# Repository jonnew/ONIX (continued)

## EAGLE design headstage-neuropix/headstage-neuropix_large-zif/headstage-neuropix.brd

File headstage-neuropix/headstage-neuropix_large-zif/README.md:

# headstage-neuropix (large ZIF)
This version of the headstage has a larger, more reliable ZIF connector.

## Bill of materials
TODO

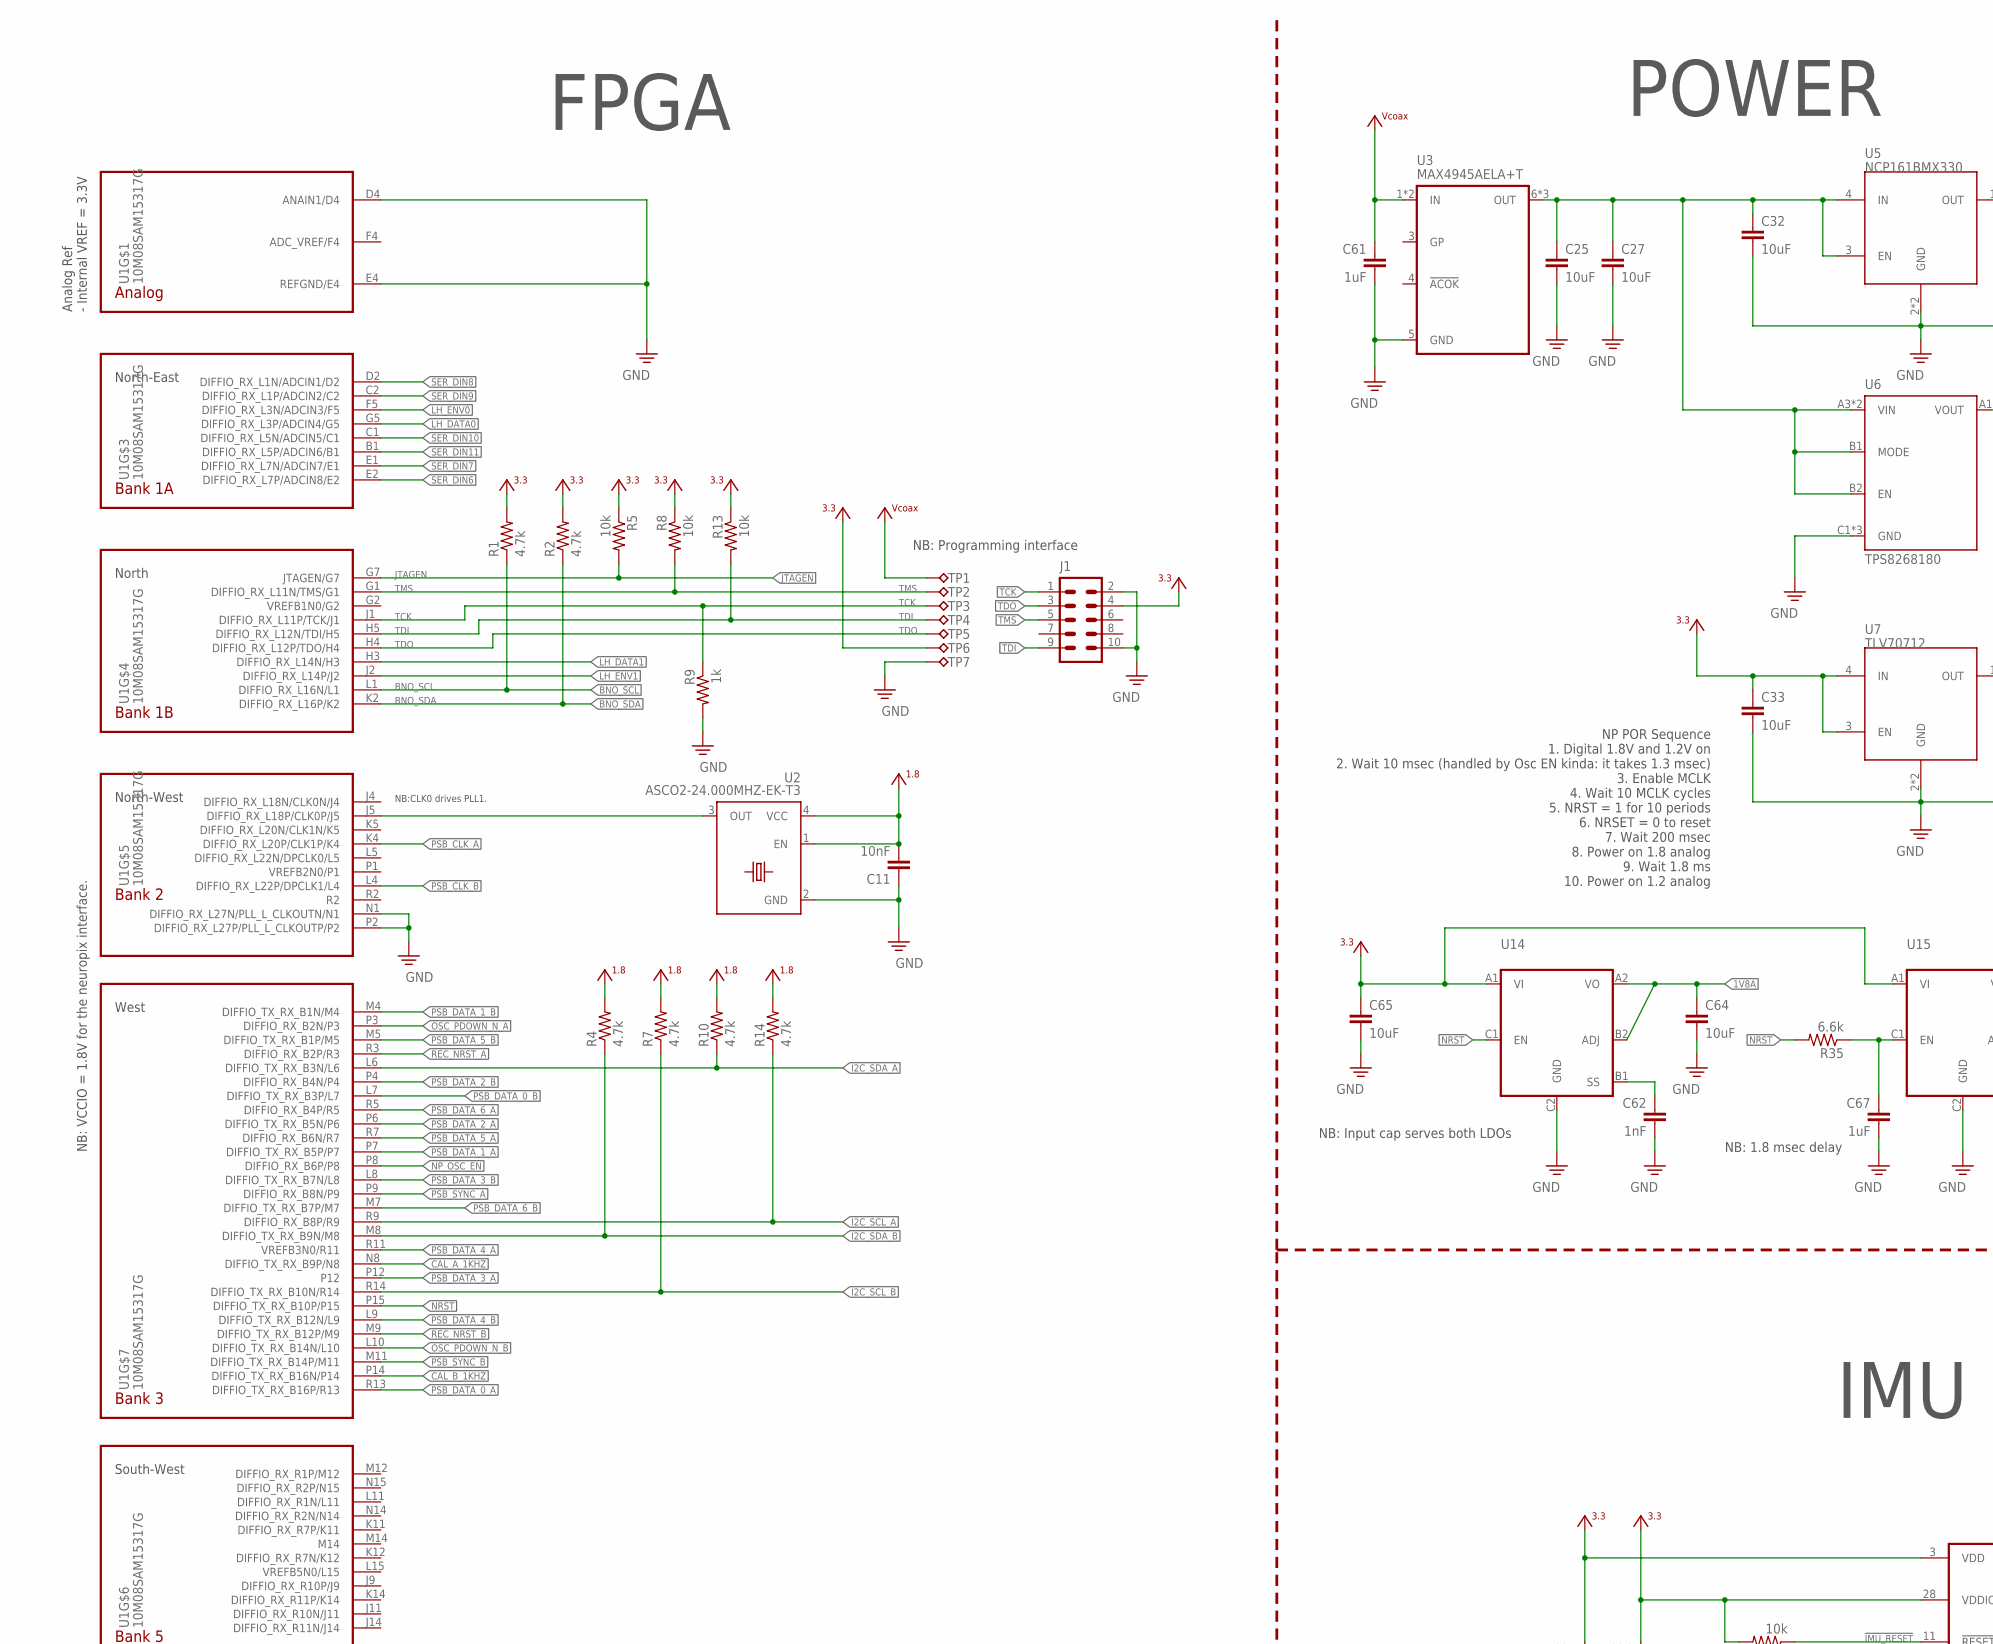
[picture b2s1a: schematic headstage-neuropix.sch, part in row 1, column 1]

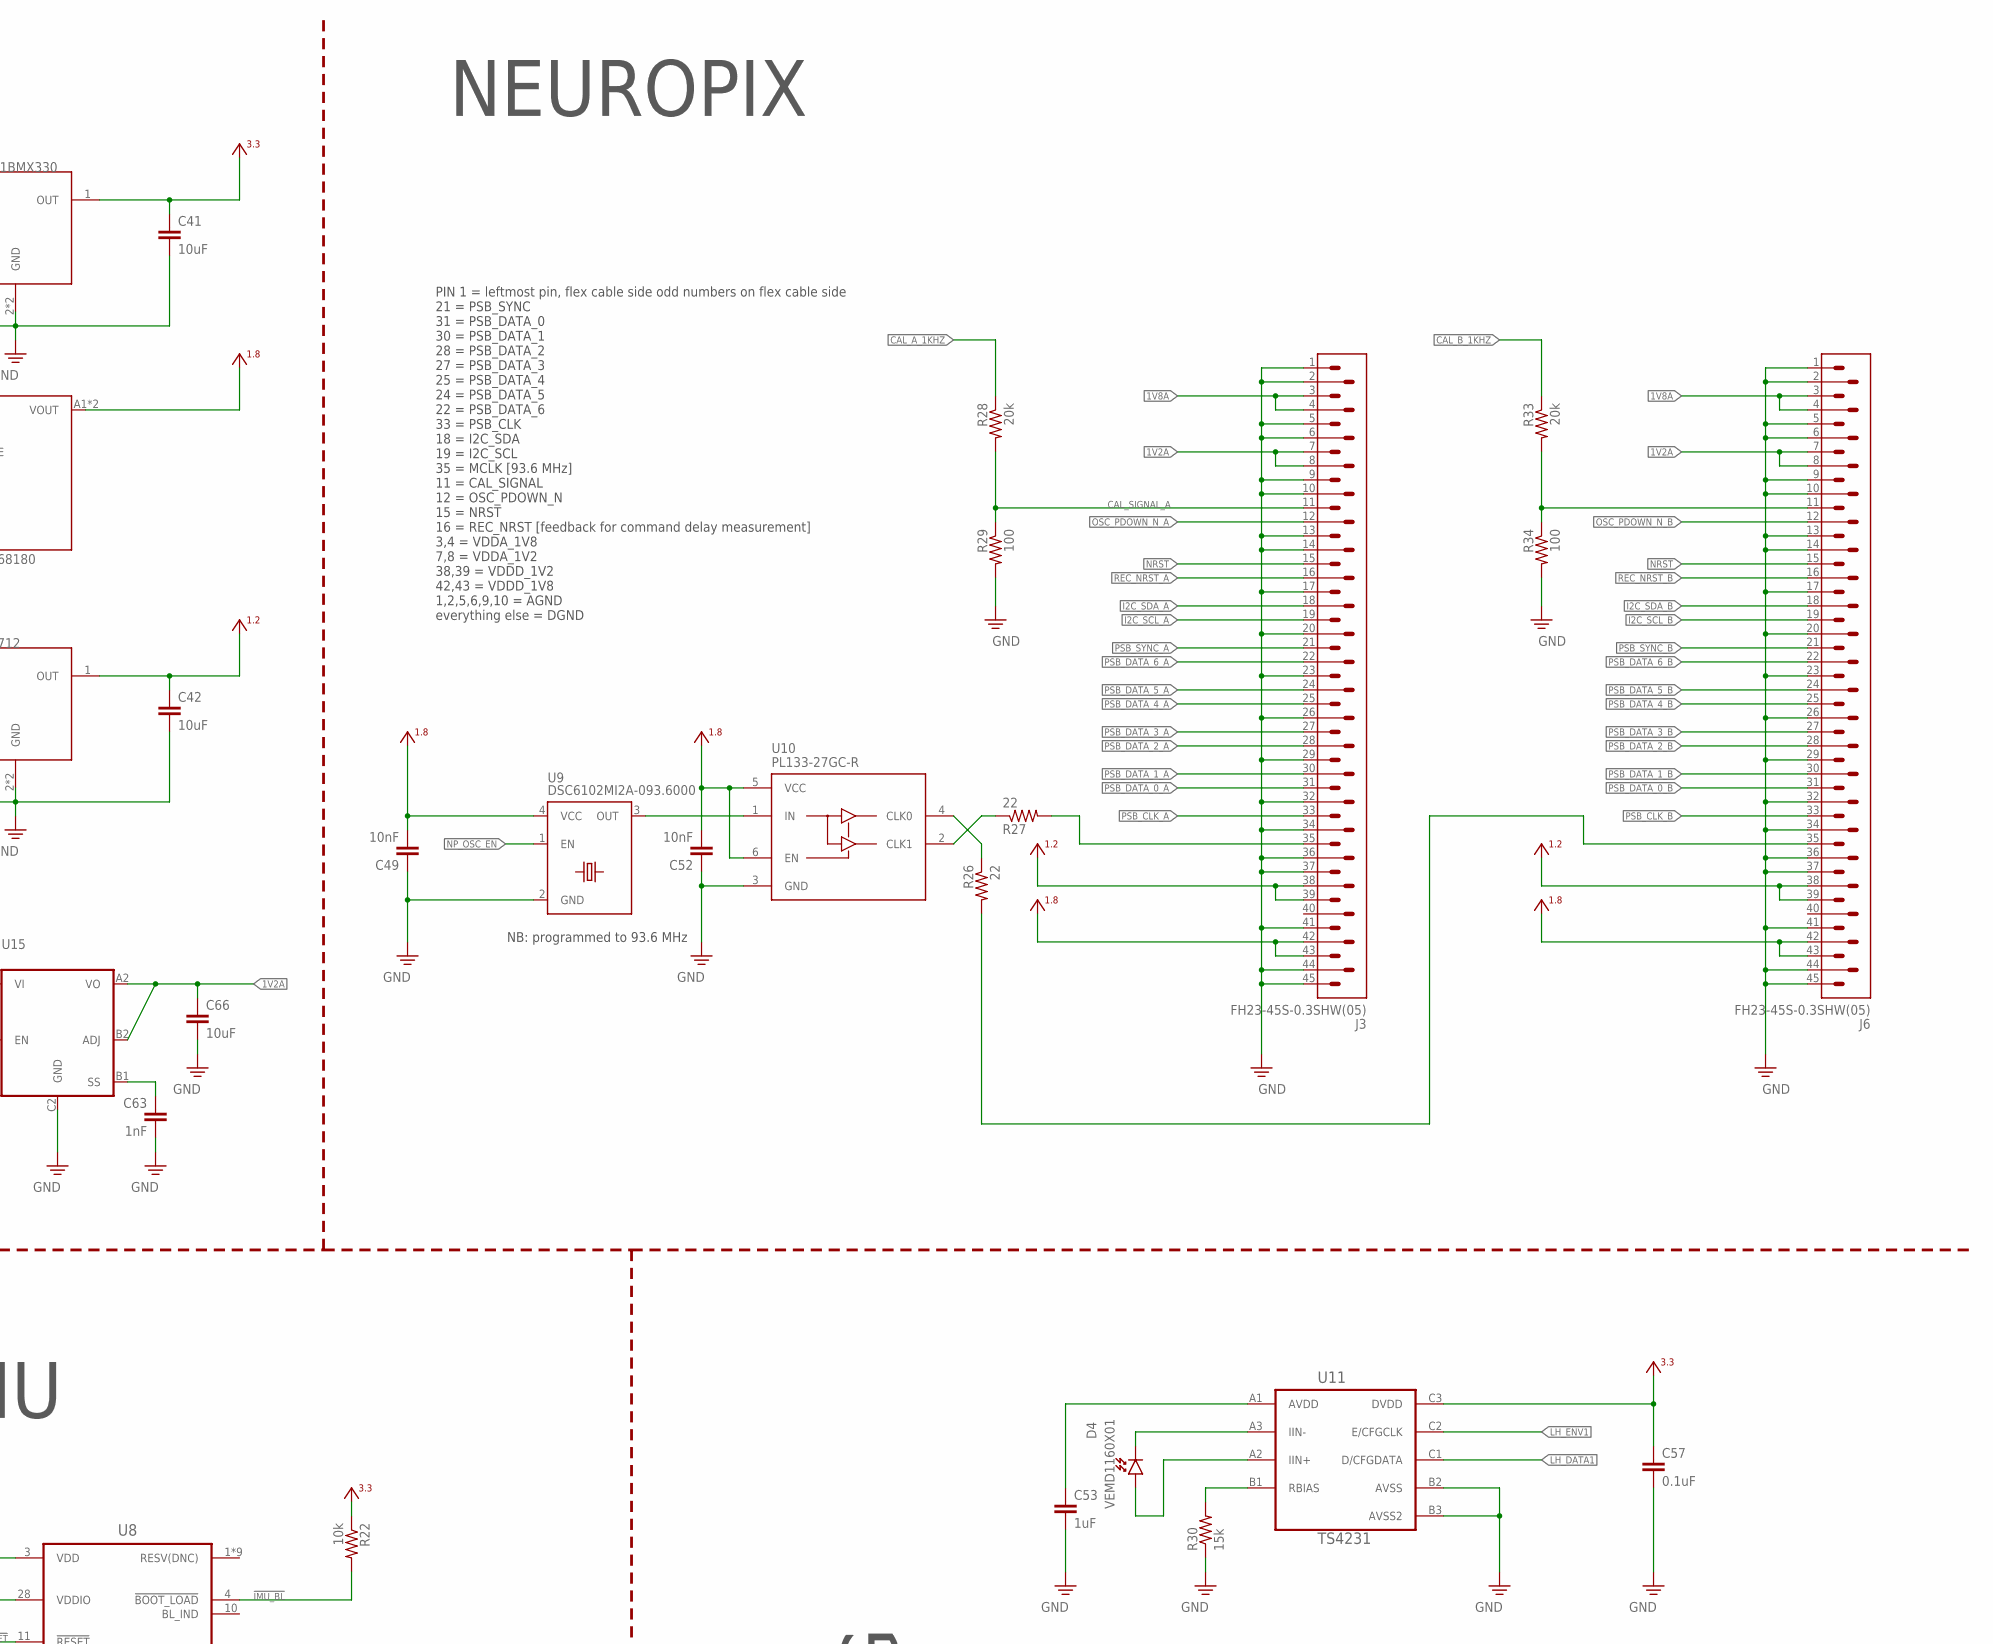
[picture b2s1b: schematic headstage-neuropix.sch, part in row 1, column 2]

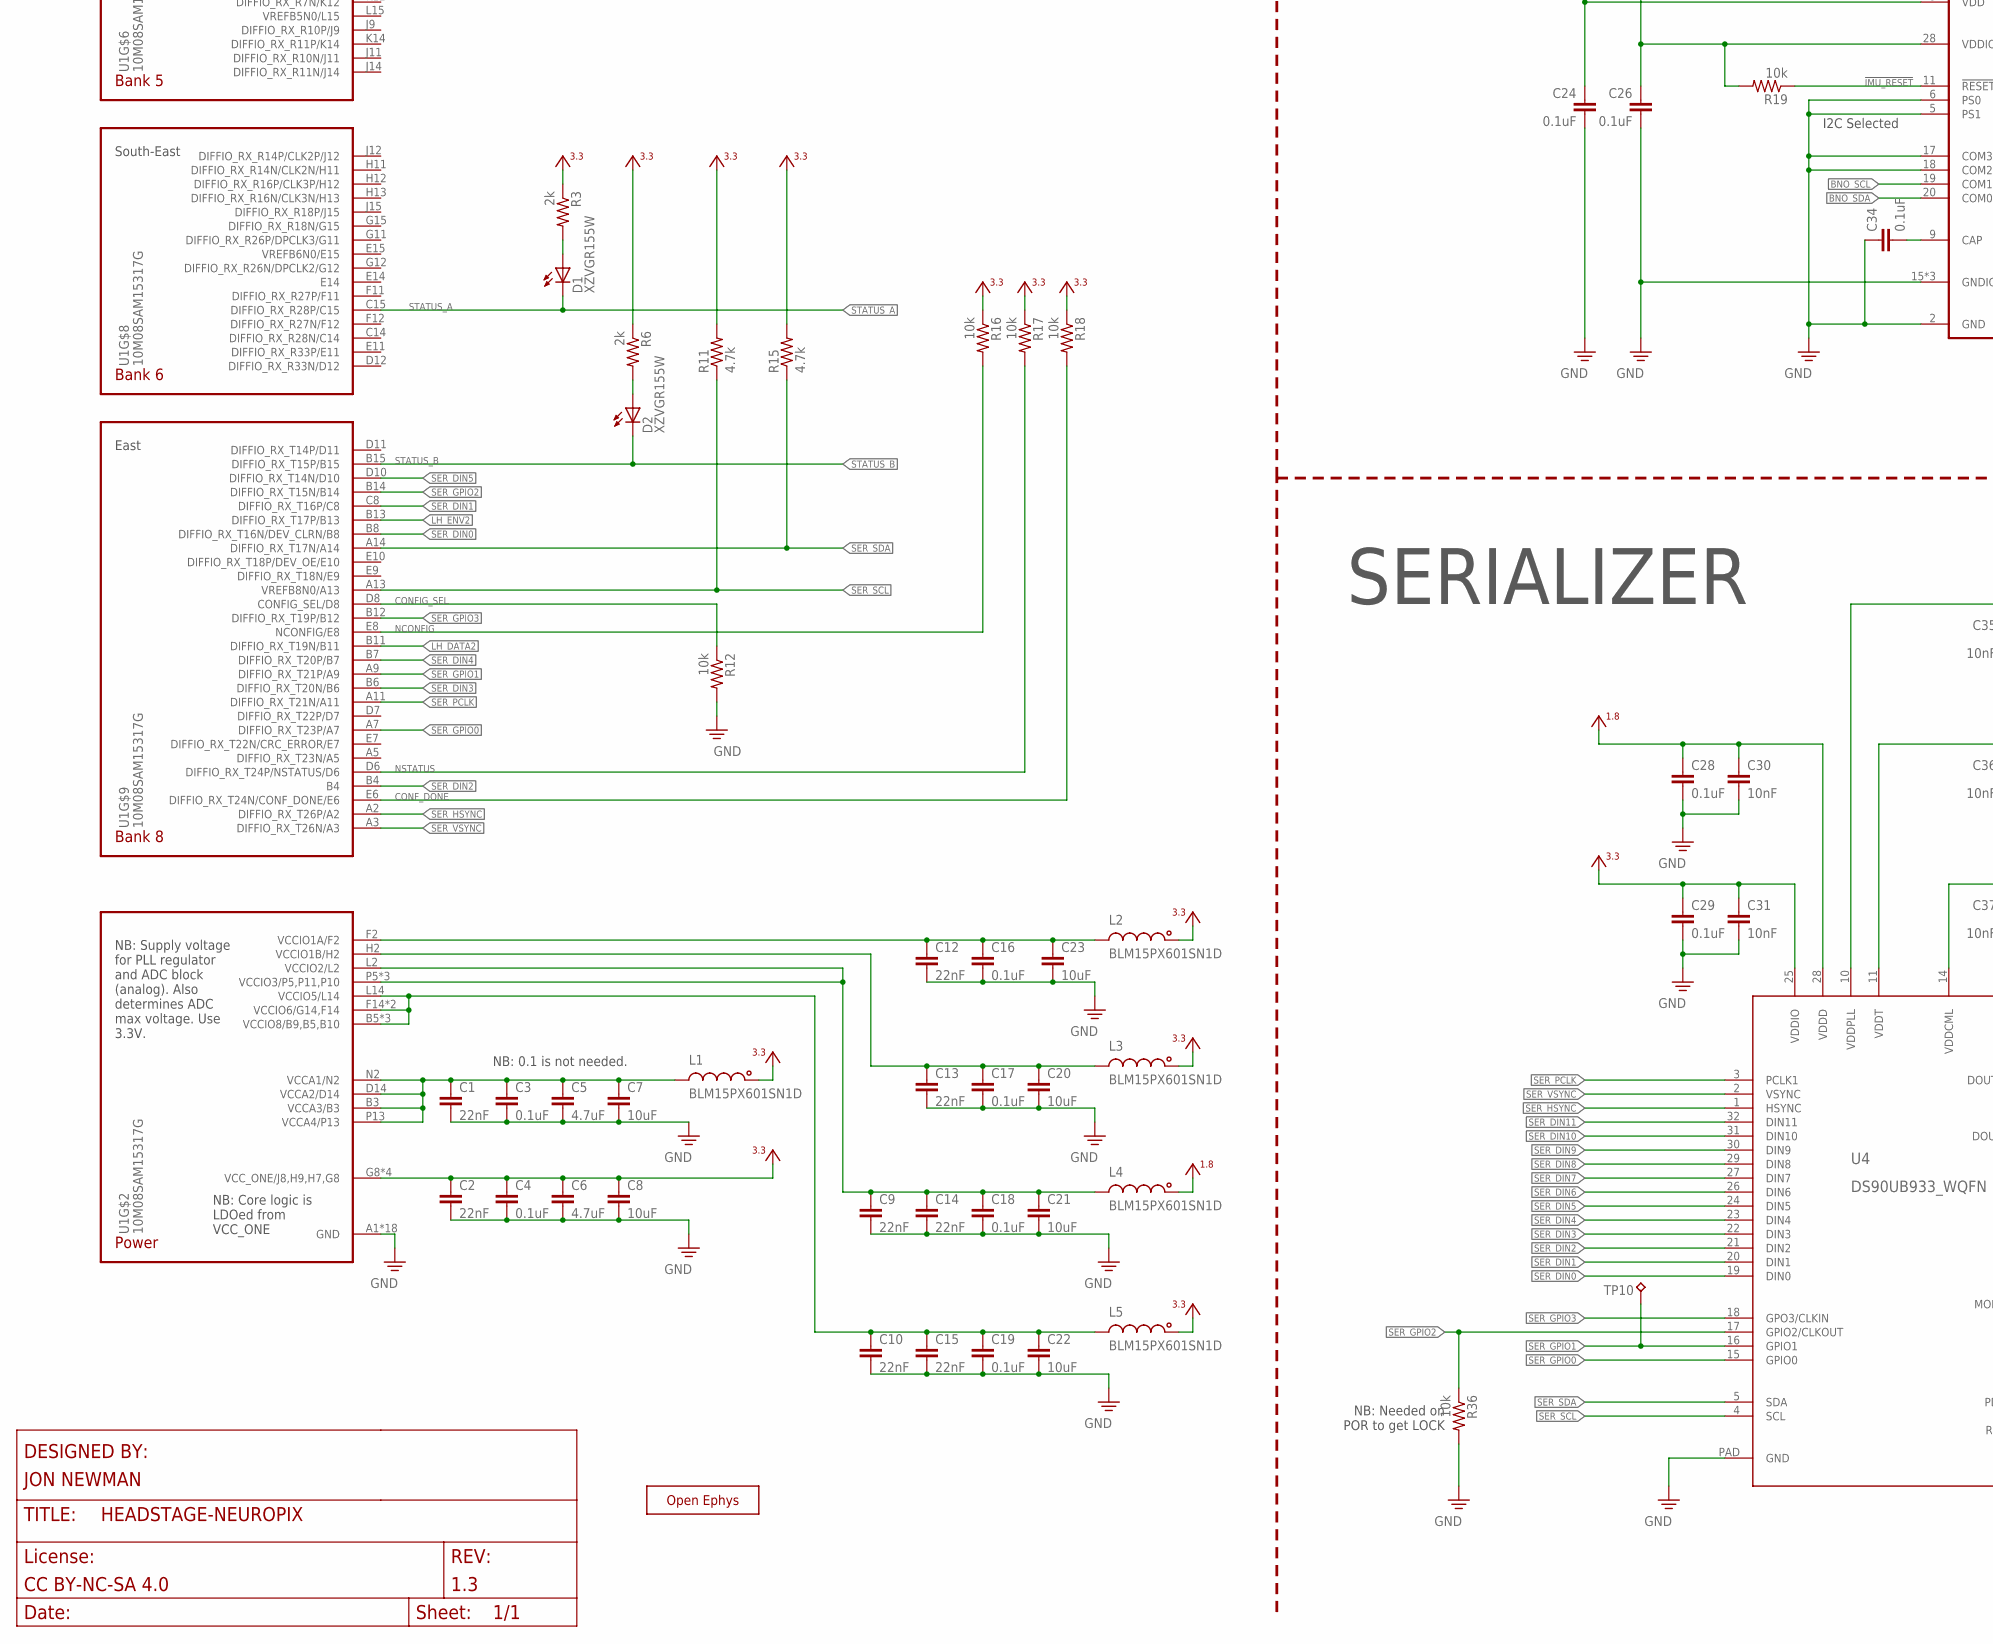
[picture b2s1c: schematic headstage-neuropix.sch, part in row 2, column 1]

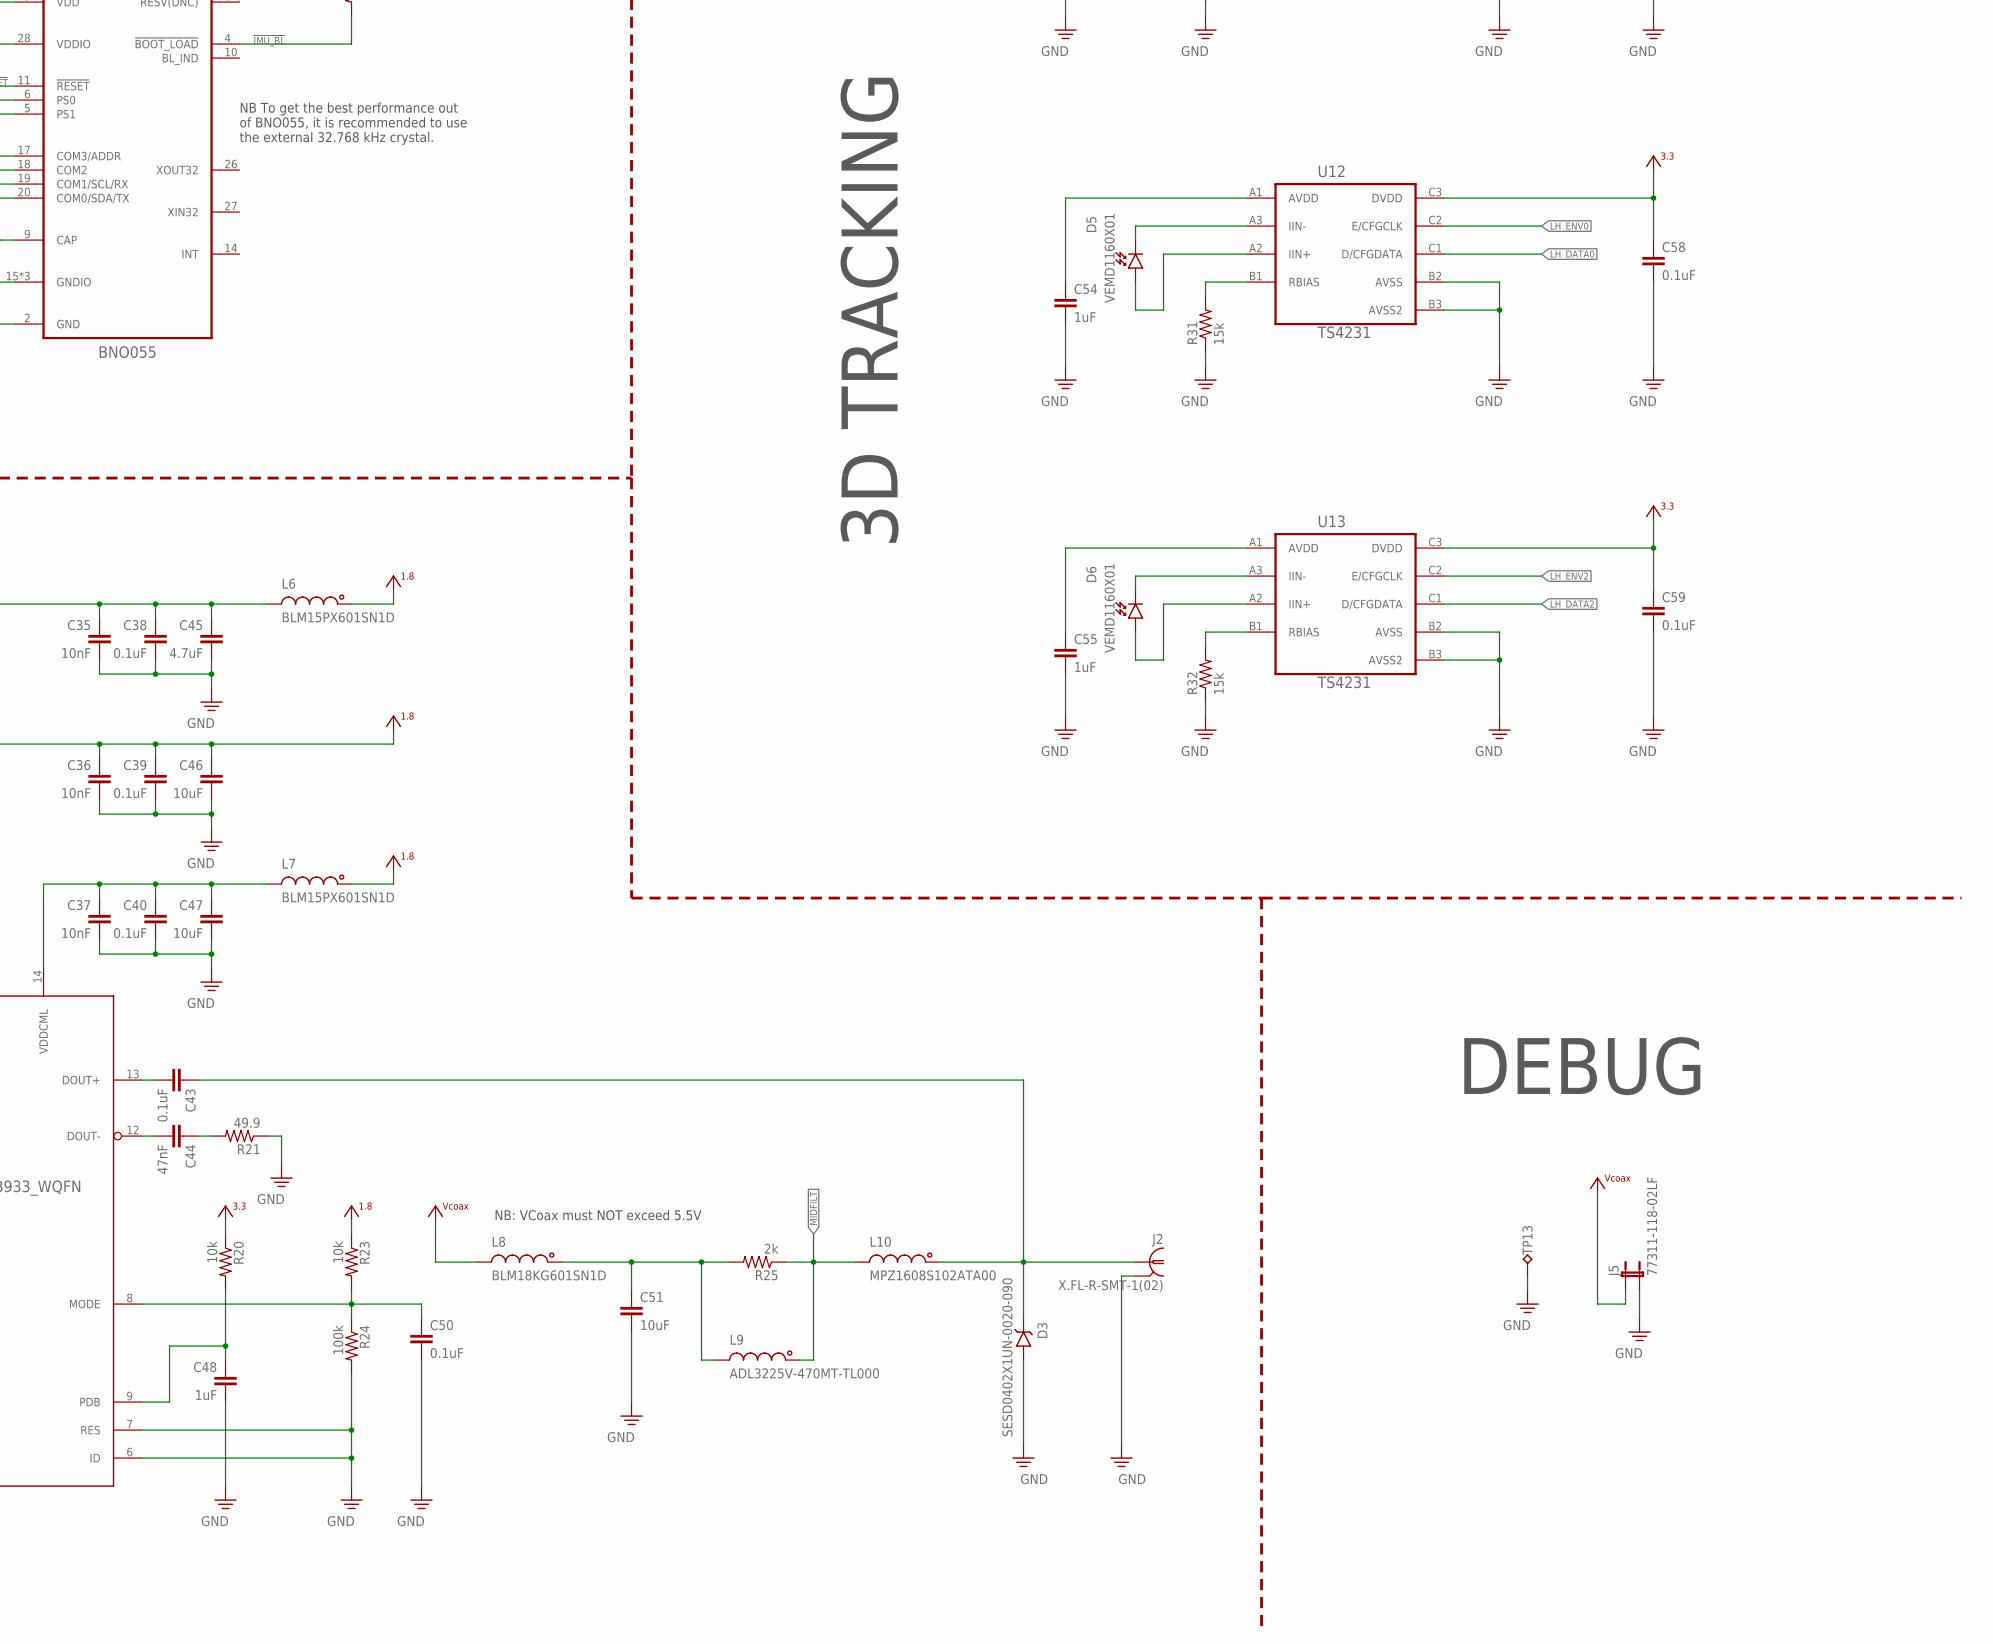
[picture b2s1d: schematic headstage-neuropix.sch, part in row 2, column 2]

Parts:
C1, C2, C9, C10, C12, C13, C14, C15: 22nF; 0201T
C3, C4, C16, C17, C18, C19, C24, C26, C28, C29, C34, C38, C39, C40, C43, C50: 0.1uF; 0201T
C5, C6, C45: 4.7uF; 0402T
C7, C8, C20, C21, C22, C23, C46, C51: 10uF; 0402T
C11, C30, C31, C35, C36, C37, C49, C52: 10nF; 0201T
C25, C27, C32, C33, C41, C42, C47, C64, C65, C66: 10uF; 0402TW
C44: 47nF; 0201T
C48, C61, C67: 1uF; 0201T
C53, C54, C55: 1uF; 0201T; PARTNO CL03A105MP3ZSNH
C57, C58, C59: 0.1uF; 0201T; PARTNO C0603X5R1C104K030BC
C62, C63: 1nF; 0201T
D1, D2: XZVGR155W; LED-0201T
D3: SESD0402X1UN-0020-090; 0402T-DFN
D4, D5, D6: VEMD1160X01; 0805PT-NOSILK
J1: 302-S101; 2X05_IDC
J2: X.FL-R-SMT-1(02); X_FL_R_SMT_1(02)
J3, J6: FH23-45S-0.3SHW(05)
J5: 77311-118-02LF; JP2
L1, L2, L3, L4, L5, L6, L7: BLM15PX601SN1D; 0402T
L8: BLM18KG601SN1D; 0603T
L9: ADL3225V-470MT-TL000; 1210T
L10: MPZ1608S102ATA00; 0603T
R1, R2, R4, R7, R10, R11, R14, R15: 4.7k; 0201T
R3, R6, R25: 2k; 0201T
R5, R8, R12, R13, R16, R17, R18, R19, R20, R22, R23, R36: 10k; 0201T
R9: 1k; 0201T
R21: 49.9; 0201T
R24: 100k; 0201T
R26, R27: 22; 0201T
R28, R33: 20k; 0201T
R29, R34: 100; 0201T
R30, R31, R32: 15k; 0201T
R35: 6.6k; 0201T
TP1, TP2, TP3, TP4, TP5, TP6, TP7: TPTP10R; TP10R
TP10: TPTP09R; TP09R
TP13: TPTP20R; TP20R
U1: 10M08SAM15317G; MBGA153-8X8
U2: ASCO2-24.000MHZ-EK-T3; ASCO
U3: MAX4945AELA+T; UDFN8-2X2
U4: DS90UB933_WQFN; WQFN32-5X5
U5: NCP161BMX330; X2SON
U6: TPS8268180; MICROSIP9-3X2.3
U7: TLV70712; X2SON
U8: BNO055; LGA-28-3.8X5.2
U9: DSC6102MI2A-093.6000; VFLGA4-2.0X1.6
U10: PL133-27GC-R; DFN6_2X1.3_PAD
U11, U12, U13: TS4231; WLCSP3X3
U14, U15: LDO_ADJUST-EN-SS_WLCSP-ADP7112; WLCSP6-1X1.2
X2: OE-LOGO_14X10; OE-LOGO-14X10

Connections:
1V2A: C66.1, J3.7, J3.8, J6.7, J6.8, U15.A2 (VO), U15.B2 (ADJ)
1V8A: C64.1, J3.3, J3.4, J6.3, J6.4, U14.A2 (VO), U14.B2 (ADJ)
24MHZ_P: U1.J5 (DIFFIO_RX_L18P/CLK0P/J5), U2.3 (OUT)
!IMU_BL: R22.2, U8.4 (!BOOT_LOAD)
!IMU_RESET: R19.1, U8.11 (!RESET)
+1V2: C42.1, J3.38, J3.39, J6.38, J6.39, U7.1 (OUT)
+1V8: C11.2, C28.1, C30.1, C36.1, C39.1, C46.1, C49.2, C52.2, J3.42, J3.43, J6.42, J6.43, L4.1, L6.1, L7.1, R4.2, R7.2, R10.2, R14.2, R23.1, U2.1 (EN), U2.4 (VCC), U4.11 (VDDT), U4.28 (VDDD), U6.A1 (VOUT), U6.A2 (VOUT), U9.4 (VCC), U10.5 (VCC), U10.6 (EN)
+3V3: C2.1, C4.1, C6.1, C8.1, C24.1, C26.1, C29.1, C31.1, C33.1, C41.1, C57.1, C58.1, C59.1, C65.1, J1.4, L1.1, L2.1, L3.1, L5.1, R1.2, R2.2, R3.1, R5.1, R6.1, R8.1, R11.2, R13.1, R15.2, R16.1, R17.1, R18.1, R19.2, R20.1, R22.1, TP6.TP, U1.G8 (VCC_ONE/J8,H9,H7,G8), U1.H7 (VCC_ONE/J8,H9,H7,G8), U1.H9 (VCC_ONE/J8,H9,H7,G8), U1.J8 (VCC_ONE/J8,H9,H7,G8), U4.25 (VDDIO), U5.1 (OUT), U7.3 (EN), U7.4 (IN), U8.3 (VDD), U8.28 (VDDIO), U11.C3 (DVDD), U12.C3 (DVDD), U13.C3 (DVDD), U14.A1 (VI), U15.A1 (VI)
BNO_SCL: R1.1, U1.L1 (DIFFIO_RX_L16N/L1), U8.19 (COM1/SCL/RX)
BNO_SDA: R2.1, U1.K2 (DIFFIO_RX_L16P/K2), U8.20 (COM0/SDA/TX)
CAL_A_1KHZ: R28.1, U1.N8 (DIFFIO_TX_RX_B9P/N8)
CAL_B_1KHZ: R33.1, U1.P14 (DIFFIO_TX_RX_B16N/P14)
CAL_SIGNAL_A: J3.11, R28.2, R29.1
CAL_SIGNAL_A1: J6.11, R33.2, R34.1
CONFIG_SEL: R12.1, U1.D8 (CONFIG_SEL/D8)
CONF_DONE: R18.2, U1.E6 (DIFFIO_RX_T24N/CONF_DONE/E6)
GND: C1.2, C2.2, C3.2, C4.2, C5.2, C6.2, C7.2, C8.2, C9.2, C10.2, C11.1, C12.2, C13.2, C14.2, C15.2, C16.2, C17.2, C18.2, C19.2, C20.2, C21.2, C22.2, C23.2, C24.2, C25.2, C26.2, C27.2, C28.2, C29.2, C30.2, C31.2, C32.2, C33.2, C34.1, C35.2, C36.2, C37.2, C38.2, C39.2, C40.2, C41.2, C42.2, C45.2, C46.2, C47.2, C48.2, C49.1, C50.2, C51.2, C52.1, C53.2, C54.2, C55.2, C57.2, C58.2, C59.2, C61.2, C62.2, C63.2, C64.2, C65.2, C66.2, C67.2, D3.A, J1.2, J1.10, J2.P$2 (2), J2.P$3 (2), J2.P$4 (2), J3.1, J3.2, J3.5, J3.6, J3.9, J3.10, J3.13, J3.14, J3.17, J3.20, J3.23, J3.26, J3.29, J3.32, J3.34, J3.36, J3.37, J3.41, J3.44, J3.45, J5.2, J6.1, J6.2, J6.5, J6.6, J6.9, J6.10, J6.13, J6.14, J6.17, J6.20, J6.23, J6.26, J6.29, J6.32, J6.34, J6.36, J6.37, J6.41, J6.44, J6.45, R9.2, R12.2, R21.1, R24.2, R29.2, R30.1, R31.1, R32.1, R34.2, R36.2, TP7.TP, TP13.TP, U1.A1 (GND), U1.A15 (GND), U1.B2 (GND), U1.D4 (ANAIN1/D4), U1.D5 (GND), U1.D9 (GND), U1.E4 (REFGND/E4), U1.E5 (GND), U1.E12 (GND), U1.G4 (GND), U1.G9 (GND), U1.H8 (GND), U1.H14 (GND), U1.J7 (GND), U1.L12 (GND), U1.M2 (GND), U1.M6 (GND), U1.M10 (GND), U1.N1 (DIFFIO_RX_L27N/PLL_L_CLKOUTN/N1), U1.P2 (DIFFIO_RX_L27P/PLL_L_CLKOUTP/P2), U1.R1 (GND), U1.R15 (GND), U2.2 (GND), U3.5 (GND), U4.6 (ID), U4.7 (RES), U4.PAD (GND), U5.2 (GND), U5.PAD (GND), U6.C1 (GND), U6.C2 (GND), U6.C3 (GND), U7.2 (GND), U7.PAD (GND), U8.2 (GND), U8.5 (PS1), U8.6 (PS0), U8.15 (GNDIO), U8.16 (GNDIO), U8.17 (COM3/ADDR), U8.18 (COM2), U8.25 (GNDIO), U9.2 (GND), U10.3 (GND), U11.B2 (AVSS), U11.B3 (AVSS2), U12.B2 (AVSS), U12.B3 (AVSS2), U13.B2 (AVSS), U13.B3 (AVSS2), U14.C2 (GND), U15.C2 (GND)
I2C_SCL_A: J3.19, R14.1, U1.R9 (DIFFIO_RX_B8P/R9)
I2C_SCL_B: J6.19, R7.1, U1.R14 (DIFFIO_TX_RX_B10N/R14)
I2C_SDA_A: J3.18, R10.1, U1.L6 (DIFFIO_TX_RX_B3N/L6)
I2C_SDA_B: J6.18, R4.1, U1.M8 (DIFFIO_TX_RX_B9N/M8)
JTAGEN: R5.2, U1.G7 (JTAGEN/G7)
LH_DATA0: U1.G5 (DIFFIO_RX_L3P/ADCIN4/G5), U12.C1 (D/CFGDATA)
LH_DATA1: U1.H3 (DIFFIO_RX_L14N/H3), U11.C1 (D/CFGDATA)
LH_DATA2: U1.B11 (DIFFIO_RX_T19N/B11), U13.C1 (D/CFGDATA)
LH_ENV0: U1.F5 (DIFFIO_RX_L3N/ADCIN3/F5), U12.C2 (E/CFGCLK)
LH_ENV1: U1.J2 (DIFFIO_RX_L14P/J2), U11.C2 (E/CFGCLK)
LH_ENV2: U1.B13 (DIFFIO_RX_T17P/B13), U13.C2 (E/CFGCLK)
MIDFILT: L9.1, L10.2, R25.1
unnamed: U9.3 (OUT), U10.1 (IN)
unnamed: R26.1, U10.4 (CLK0)
unnamed: J3.35, R27.2
unnamed: C13.1, C17.1, C20.1, L3.2, U1.H2 (VCCIO1B/H2)
unnamed: J6.35, R26.2
unnamed: R27.1, U10.2 (CLK1)
unnamed: D4.C, U11.A3 (IIN-)
unnamed: D4.A, U11.A2 (IIN+)
unnamed: R30.2, U11.B1 (RBIAS)
unnamed: C53.1, U11.A1 (AVDD)
unnamed: C51.1, L8.1, L9.2, R25.2
unnamed: D5.C, U12.A3 (IIN-)
unnamed: D5.A, U12.A2 (IIN+)
unnamed: R31.2, U12.B1 (RBIAS)
unnamed: D6.C, U13.A3 (IIN-)
unnamed: D6.A, U13.A2 (IIN+)
unnamed: C43.2, U4.13 (DOUT+)
unnamed: R32.2, U13.B1 (RBIAS)
unnamed: C48.1, R20.2, U4.9 (PDB)
unnamed: C44.2, U4.12 (DOUT-)
unnamed: C44.1, R21.2
unnamed: C50.1, R23.2, R24.1, U4.8 (MODE)
unnamed: C35.1, C38.1, C45.1, L6.2, U4.10 (VDDPLL)
unnamed: C37.1, C40.1, C47.1, L7.2, U4.14 (VDDCML)
unnamed: C54.1, U12.A1 (AVDD)
unnamed: C55.1, U13.A1 (AVDD)
unnamed: C25.1, C27.1, C32.1, U3.6 (OUT), U3.7 (OUT), U3.8 (OUT), U5.3 (EN), U5.4 (IN), U6.A3 (VIN), U6.B1 (MODE), U6.B2 (EN), U6.B3 (VIN)
unnamed: C62.1, U14.B1 (SS)
unnamed: C63.1, U15.B1 (SS)
unnamed: C67.1, R35.1, U15.C1 (EN)
unnamed: C34.2, U8.9 (CAP)
unnamed: D2.2 (A), R6.2
unnamed: D1.2 (A), R3.2
NCONFIG: R16.2, U1.E8 (NCONFIG/E8)
NP_OSC_EN: U1.P8 (DIFFIO_RX_B6P/P8), U9.1 (EN)
NRST: J3.15, J6.15, R35.2, U1.P15 (DIFFIO_TX_RX_B10P/P15), U14.C1 (EN)
NSTATUS: R17.2, U1.D6 (DIFFIO_RX_T24P/NSTATUS/D6)
OSC_PDOWN_N_A: J3.12, U1.P3 (DIFFIO_RX_B2N/P3)
OSC_PDOWN_N_B: J6.12, U1.L10 (DIFFIO_TX_RX_B14N/L10)
PSB_CLK_A: J3.33, U1.K4 (DIFFIO_RX_L20P/CLK1P/K4)
PSB_CLK_B: J6.33, U1.L4 (DIFFIO_RX_L22P/DPCLK1/L4)
PSB_DATA_0_A: J3.31, U1.R13 (DIFFIO_TX_RX_B16P/R13)
PSB_DATA_0_B: J6.31, U1.L7 (DIFFIO_TX_RX_B3P/L7)
PSB_DATA_1_A: J3.30, U1.P7 (DIFFIO_TX_RX_B5P/P7)
PSB_DATA_1_B: J6.30, U1.M4 (DIFFIO_TX_RX_B1N/M4)
PSB_DATA_2_A: J3.28, U1.P6 (DIFFIO_TX_RX_B5N/P6)
PSB_DATA_2_B: J6.28, U1.P4 (DIFFIO_RX_B4N/P4)
PSB_DATA_3_A: J3.27, U1.P12
PSB_DATA_3_B: J6.27, U1.L8 (DIFFIO_TX_RX_B7N/L8)
PSB_DATA_4_A: J3.25, U1.R11 (VREFB3N0/R11)
PSB_DATA_4_B: J6.25, U1.L9 (DIFFIO_TX_RX_B12N/L9)
PSB_DATA_5_A: J3.24, U1.R7 (DIFFIO_RX_B6N/R7)
PSB_DATA_5_B: J6.24, U1.M5 (DIFFIO_TX_RX_B1P/M5)
PSB_DATA_6_A: J3.22, U1.R5 (DIFFIO_RX_B4P/R5)
PSB_DATA_6_B: J6.22, U1.M7 (DIFFIO_TX_RX_B7P/M7)
PSB_SYNC_A: J3.21, U1.P9 (DIFFIO_RX_B8N/P9)
PSB_SYNC_B: J6.21, U1.M11 (DIFFIO_TX_RX_B14P/M11)
REC_NRST_A: J3.16, U1.R3 (DIFFIO_RX_B2P/R3)
REC_NRST_B: J6.16, U1.M9 (DIFFIO_TX_RX_B12P/M9)
SER_DIN0: U1.B8 (DIFFIO_RX_T16N/DEV_CLRN/B8), U4.19 (DIN0)
SER_DIN1: U1.C8 (DIFFIO_RX_T16P/C8), U4.20 (DIN1)
SER_DIN2: U1.B4, U4.21 (DIN2)
SER_DIN3: U1.B6 (DIFFIO_RX_T20N/B6), U4.22 (DIN3)
SER_DIN4: U1.B7 (DIFFIO_RX_T20P/B7), U4.23 (DIN4)
SER_DIN5: U1.D10 (DIFFIO_RX_T14N/D10), U4.24 (DIN5)
SER_DIN6: U1.E2 (DIFFIO_RX_L7P/ADCIN8/E2), U4.26 (DIN6)
SER_DIN7: U1.E1 (DIFFIO_RX_L7N/ADCIN7/E1), U4.27 (DIN7)
SER_DIN8: U1.D2 (DIFFIO_RX_L1N/ADCIN1/D2), U4.29 (DIN8)
SER_DIN9: U1.C2 (DIFFIO_RX_L1P/ADCIN2/C2), U4.30 (DIN9)
SER_DIN10: U1.C1 (DIFFIO_RX_L5N/ADCIN5/C1), U4.31 (DIN10)
SER_DIN11: U1.B1 (DIFFIO_RX_L5P/ADCIN6/B1), U4.32 (DIN11)
SER_GPIO0: U1.A7 (DIFFIO_RX_T23P/A7), U4.15 (GPIO0)
SER_GPIO1: TP10.TP, U1.A9 (DIFFIO_RX_T21P/A9), U4.16 (GPIO1)
SER_GPIO2: R36.1, U1.B14 (DIFFIO_RX_T15N/B14), U4.17 (GPIO2/CLKOUT)
SER_GPIO3: U1.B12 (DIFFIO_RX_T19P/B12), U4.18 (GPO3/CLKIN)
SER_HSYNC: U1.A2 (DIFFIO_RX_T26P/A2), U4.1 (HSYNC)
SER_PCLK: U1.A11 (DIFFIO_RX_T21N/A11), U4.3 (PCLK1)
SER_SCL: R11.1, U1.A13 (VREFB8N0/A13), U4.4 (SCL)
SER_SDA: R15.1, U1.A14 (DIFFIO_RX_T17N/A14), U4.5 (SDA)
SER_VSYNC: U1.A3 (DIFFIO_RX_T26N/A3), U4.2 (VSYNC)
SIGOUT: C43.1, D3.C, J2.P$1 (1), L10.1
STATUS_A: D1.1 (C), U1.C15 (DIFFIO_RX_R28P/C15)
STATUS_B: D2.1 (C), U1.B15 (DIFFIO_RX_T15P/B15)
TCK: J1.1, R9.1, TP3.TP, U1.J1 (DIFFIO_RX_L11P/TCK/J1)
TDI: J1.9, R13.2, TP4.TP, U1.H5 (DIFFIO_RX_L12N/TDI/H5)
TDO: J1.3, TP5.TP, U1.H4 (DIFFIO_RX_L12P/TDO/H4)
TMS: J1.5, R8.2, TP2.TP, U1.G1 (DIFFIO_RX_L11N/TMS/G1)
VCCA: C1.1, C3.1, C5.1, C7.1, L1.2, U1.B3 (VCCA3/B3), U1.D14 (VCCA2/D14), U1.N2 (VCCA1/N2), U1.P13 (VCCA4/P13)
VCCIO: C10.1, C15.1, C19.1, C22.1, L5.2, U1.B5 (VCCIO8/B9,B5,B10), U1.B9 (VCCIO8/B9,B5,B10), U1.B10 (VCCIO8/B9,B5,B10), U1.F14 (VCCIO6/G14,F14), U1.G14 (VCCIO6/G14,F14), U1.L14 (VCCIO5/L14)
VCCIO2: C9.1, C14.1, C18.1, C21.1, L4.2, U1.L2 (VCCIO2/L2), U1.P5 (VCCIO3/P5,P11,P10), U1.P10 (VCCIO3/P5,P11,P10), U1.P11 (VCCIO3/P5,P11,P10)
VCCIOA: C12.1, C16.1, C23.1, L2.2, U1.F2 (VCCIO1A/F2)
VCOAX: C61.1, J5.1, L8.2, TP1.TP, U3.1 (IN), U3.2 (IN)

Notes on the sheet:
NB: VCoax must NOT exceed 5.5V
SERIALIZER
POWER
NEUROPIX
DEBUG
PIN 1 = leftmost pin, flex cable side odd numbers on flex cable side 21 = PSB_SYNC 31 = PSB_DATA_0 30 = PSB_DATA_1 28 = PSB_DATA_2 27 = PSB_DATA_3 25 = PSB_DATA_4 24 = PSB_DATA_5 22 = PSB_DATA_6 33 = PSB_CLK 18 = I2C_SDA 19 = I2C_SCL 35 = MCLK [93.6 MHz] 11 = CAL_SIGNAL 12 = OSC_PDOWN_N 15 = NRST 1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
NB: Core logic is LDOed from VCC_ONE
NB: Supply voltage for PLL regulator and ADC block (analog). Also determines ADC max voltage. Use 3.3V.
NB: VCCIO = 1.8V for the neuropix interface.
FPGA
South-East
East
South-West
West
North-West
North
North-East
Analog Ref - Internal VREF = 3.3V
NB: Programming interface
NB: 0.1 is not needed.
NB:CLK0 drives PLL1.
IMU
I2C Selected
NB To get the best performance out of BNO055, it is recommended to use the external 32.768 kHz crystal.
3D TRACKING
NB: programmed to 93.6 MHz
NP POR Sequence 1. Digital 1.8V and 1.2V on 2. Wait 10 msec (handled by Osc EN kinda: it takes 1.3 msec) 3. Enable MCLK 4. Wait 10 MCLK cycles 5. NRST = 1 for 10 periods 6. NRSET = 0 to reset 7. Wait 200 msec 8. Power on 1.8 analog 9. Wait 1.8 ms 10. Power on 1.2 analog
NB: 1.8 msec delay
NB: Input cap serves both LDOs
NB: Needed on POR to get LOCK

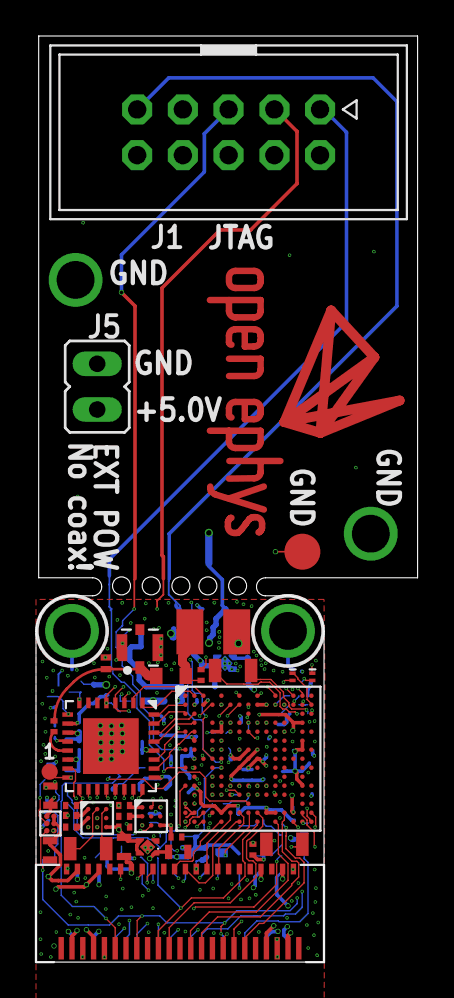
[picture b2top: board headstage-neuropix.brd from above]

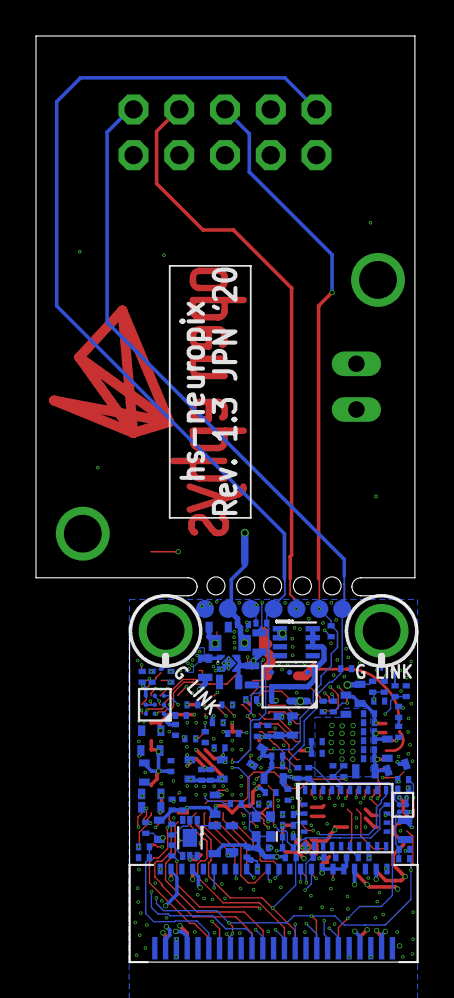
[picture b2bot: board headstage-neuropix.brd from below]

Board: 6 copper layers, 21.2 x 51.5 mm, 147 parts (112 on the bottom side), 121 nets.
